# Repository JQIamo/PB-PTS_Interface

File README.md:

# PB-PTS_Interface

## Project Location
Find us on GitHub: http://git.io/vc0xU or directly https://github.com/JQIamo/PB-PTS_Interface/

 [PB-PTS_Interface](https://github.com/JQIamo/PB-PTS_Interface/) is licensed under a [Creative Commons Attribution-ShareAlike 4.0 International License](http://creativecommons.org/licenses/by-sa/4.0/).

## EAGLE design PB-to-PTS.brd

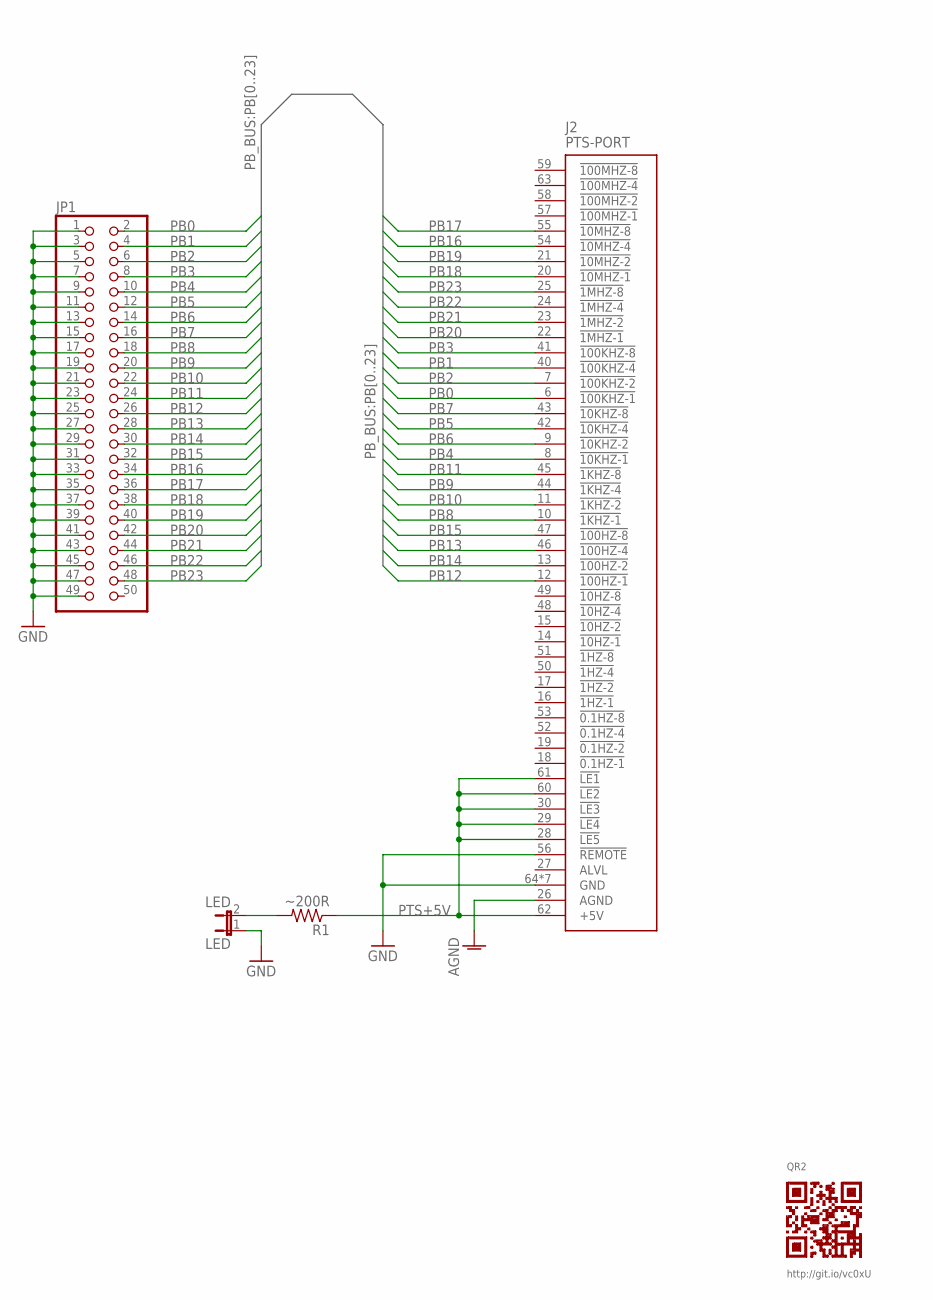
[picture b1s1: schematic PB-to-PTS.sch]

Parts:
J2: PTS-PORT; MOLEX-73776-0201
JP1: PINHD-2X25; 2X25
LED: LED; JP1
QR2: QR-HTTP://GIT.IO/VC0XU
R1: ~200R; R0805

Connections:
AGND: J2.26 (AGND)
GND: J2.56 (!REMOTE), J2.64 (GND), J2.SHIELD1 (GND), J2.SHIELD2 (GND), J2.SHIELD3 (GND), J2.SHIELD4 (GND), J2.SHIELD5 (GND), J2.SHIELD6 (GND), JP1.1, JP1.3, JP1.5, JP1.7, JP1.9, JP1.11, JP1.13, JP1.15, JP1.17, JP1.19, JP1.21, JP1.23, JP1.25, JP1.27, JP1.29, JP1.31, JP1.33, JP1.35, JP1.37, JP1.39, JP1.41, JP1.43, JP1.45, JP1.47, JP1.49, LED.1
unnamed: LED.2, R1.2
PB0: J2.6 (!100KHZ-1), JP1.2
PB1: J2.40 (!100KHZ-4), JP1.4
PB2: J2.7 (!100KHZ-2), JP1.6
PB3: J2.41 (!100KHZ-8), JP1.8
PB4: J2.8 (!10KHZ-1), JP1.10
PB5: J2.42 (!10KHZ-4), JP1.12
PB6: J2.9 (!10KHZ-2), JP1.14
PB7: J2.43 (!10KHZ-8), JP1.16
PB8: J2.10 (!1KHZ-1), JP1.18
PB9: J2.44 (!1KHZ-4), JP1.20
PB10: J2.11 (!1KHZ-2), JP1.22
PB11: J2.45 (!1KHZ-8), JP1.24
PB12: J2.12 (!100HZ-1), JP1.26
PB13: J2.46 (!100HZ-4), JP1.28
PB14: J2.13 (!100HZ-2), JP1.30
PB15: J2.47 (!100HZ-8), JP1.32
PB16: J2.54 (!10MHZ-4), JP1.34
PB17: J2.55 (!10MHZ-8), JP1.36
PB18: J2.20 (!10MHZ-1), JP1.38
PB19: J2.21 (!10MHZ-2), JP1.40
PB20: J2.22 (!1MHZ-1), JP1.42
PB21: J2.23 (!1MHZ-2), JP1.44
PB22: J2.24 (!1MHZ-4), JP1.46
PB23: J2.25 (!1MHZ-8), JP1.48
PTS+5V: J2.28 (!LE5), J2.29 (!LE4), J2.30 (!LE3), J2.60 (!LE2), J2.61 (!LE1), J2.62 (+5V), R1.1

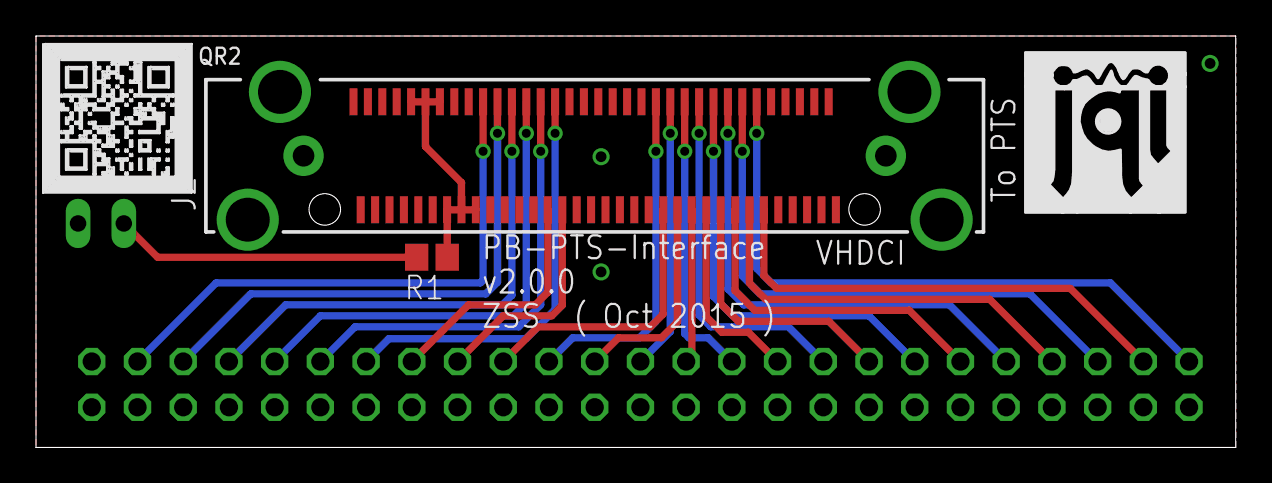
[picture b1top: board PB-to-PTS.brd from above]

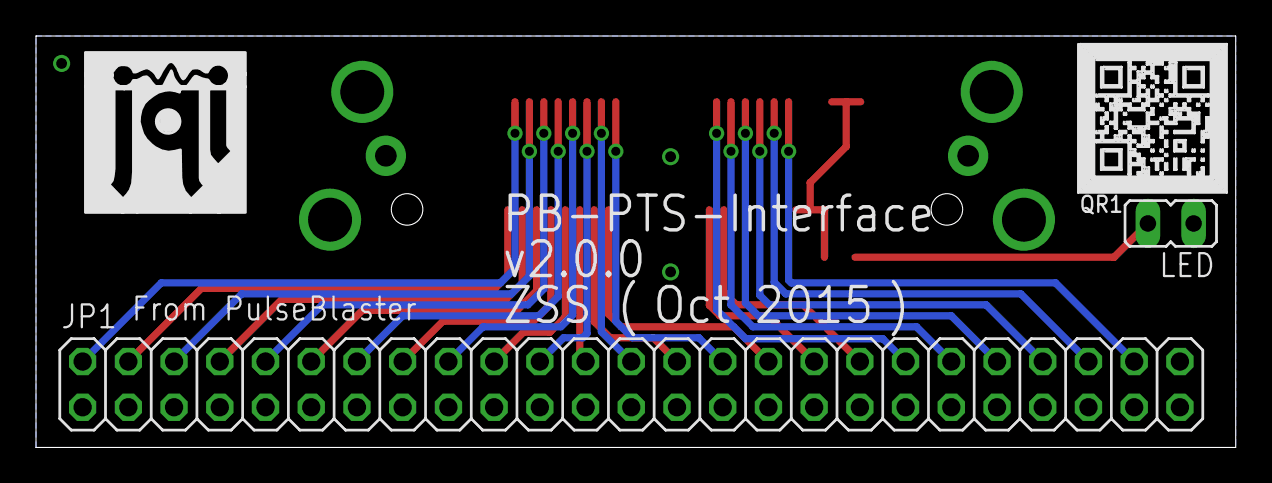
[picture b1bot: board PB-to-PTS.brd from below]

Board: 2 copper layers, 66.6 x 22.9 mm, 10 parts (5 on the bottom side), 27 nets.

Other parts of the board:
QR1: QR-HTTP://GIT.IO/VC0XU
U$3, U$4: JQI_LOGO_NEGATIVE-SILKSCREEN
U$5: INFO_BLOCK-0.05
U$6: INFO_BLOCK-0.076

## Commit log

2015-10-01 Add QR Code Library to project
2015-10-01 Clean up schematic, route board
2015-10-01 Remove tStop box
2015-10-01 Fix Double-V on board revision, October->Oct
    Changed the info block to not automatically include the v, so
    the revision no longer prints as 'vv2.0.0'.
    Changed the month from 'October 2015' to 'Oct 2015' so it would fit.

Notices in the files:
README.md:
License: Creative Commons BY-SA 4.0
